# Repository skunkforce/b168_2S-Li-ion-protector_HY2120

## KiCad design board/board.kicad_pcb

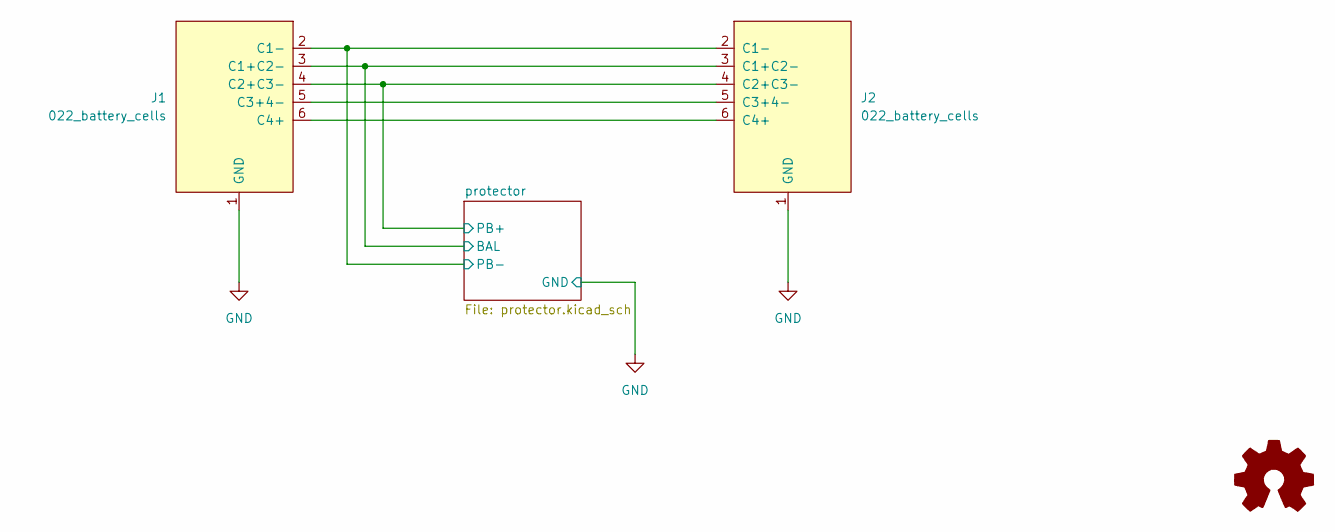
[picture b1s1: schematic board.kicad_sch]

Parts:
J1: 022_battery_cells; on_edge_2x05_device
J2: 022_battery_cells; on_edge_2x05_host
LOGO1: Logo_Open_Hardware_Small; OSHW-Symbol_6.7x6mm_SilkScreen

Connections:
/protector/BAL: J1.3 (C1+C2-), J2.3 (C1+C2-); also elsewhere on the board
/protector/PB+: J1.4 (C2+C3-), J2.4 (C2+C3-); also elsewhere on the board
/protector/PB-: J1.2 (C1-), J2.2 (C1-); also elsewhere on the board
GND: J1.1 (GND), J2.1 (GND); also elsewhere on the board
unnamed: J1.5 (C3+4-), J2.5 (C3+4-)
unnamed: J1.6 (C4+), J2.6 (C4+)

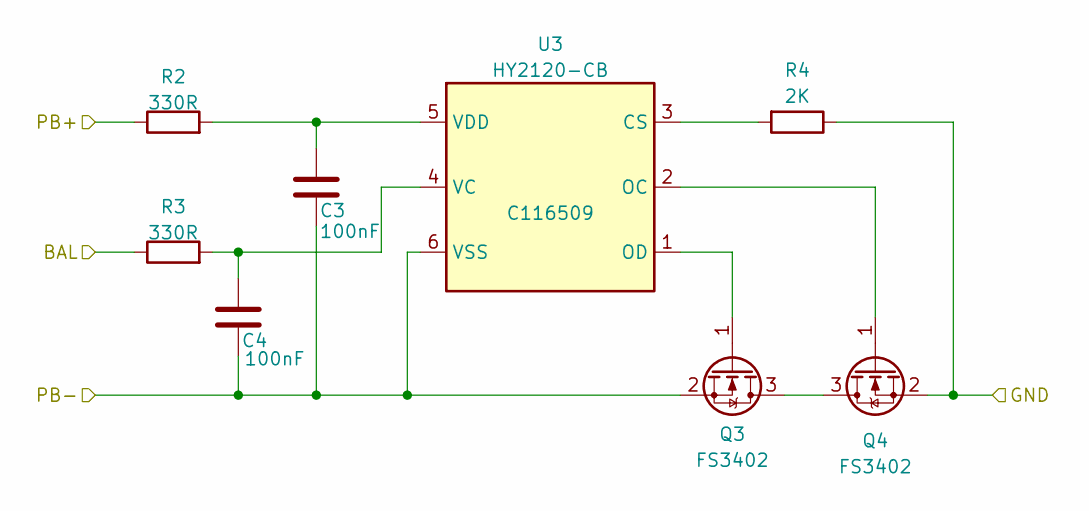
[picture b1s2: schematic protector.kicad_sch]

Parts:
C3, C4: 100nF; C_0603_1608Metric; LCSC C83054
Q3, Q4: FS3402; SOT-23; LCSC C2926128
R2, R3: 330R; R_0603_1608Metric; LCSC C2907152
R4: 2K; R_0603_1608Metric; LCSC C2907137
U3: HY2120-CB; SOT-23-6; LCSC C116509

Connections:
/protector/BAL: R3.1; also elsewhere on the board
/protector/PB+: R2.1; also elsewhere on the board
/protector/PB-: C3.2, C4.2, Q3.2 (S), U3.6 (VSS); also elsewhere on the board
GND: Q4.2 (S), R4.1; also elsewhere on the board
unnamed: Q3.3 (D), Q4.3 (D)
unnamed: Q3.1 (G), U3.1 (OD)
unnamed: Q4.1 (G), U3.2 (OC)
unnamed: R4.2, U3.3 (CS)
unnamed: C4.1, R3.2, U3.4 (VC)
unnamed: C3.1, R2.2, U3.5 (VDD)

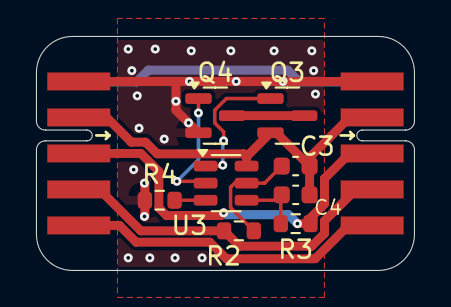
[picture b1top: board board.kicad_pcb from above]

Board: 2 copper layers, 21.0 x 13.0 mm, 11 parts (1 on the bottom side), 12 nets.

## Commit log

2025-04-30 initial
